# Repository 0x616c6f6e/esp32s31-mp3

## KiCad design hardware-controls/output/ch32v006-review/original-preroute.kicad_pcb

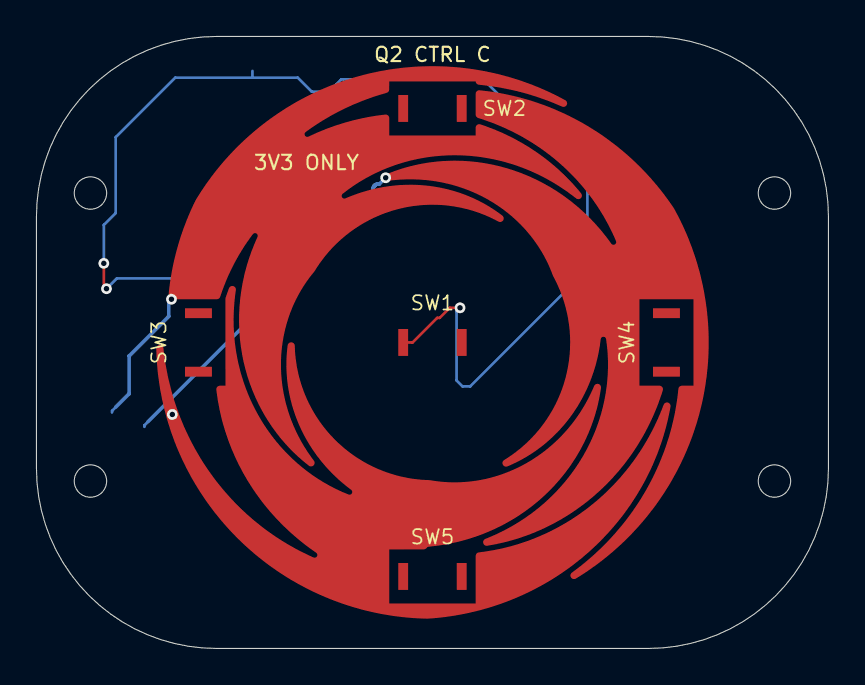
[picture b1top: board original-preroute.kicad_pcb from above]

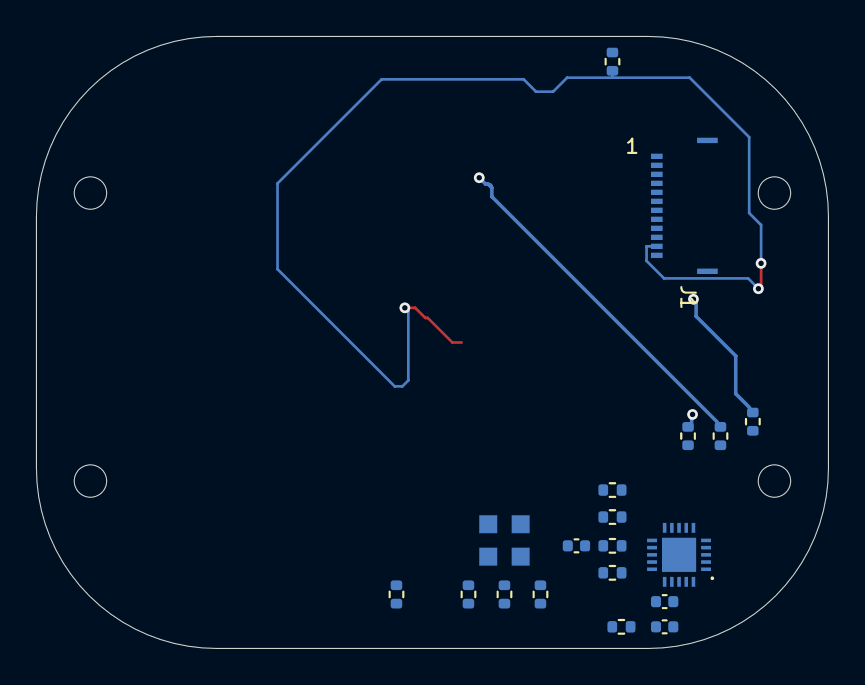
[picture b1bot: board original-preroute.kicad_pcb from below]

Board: 2 copper layers, 44.0 x 34.0 mm, 29 parts (19 on the bottom side), 19 nets.

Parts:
C1, C3: 100nF; C0402
C2: 1uF; C0402
E1: 31mm INTERPOLATED WHEEL; Wheel_D31
H1, H2, H3, H4: M1.6 / NPTH 1.8; Mount_1.8
J1: HC-FPC-05-10-12RLTAG; HCTL_FPC12
J2: WCH_SDI_PADS; SDI_4_Pads
R1, R2, R3: 1k; R0402
R4, R5: 4.7k; R0402
R6, R7, R14: 10k; R0402
R8: 0R; R0402
R9, R10, R11, R12: 47k; R0402
SW1, SW2, SW3, SW4, SW5: SKSWCEE010; SKSW_3x2
U1: CH32V006F8U6; CH32V006_QFN20

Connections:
/+3V3: J1.2, R4.1, R5.1, R6.1, R7.1, R8.1, R9.1, R10.1, R11.1, R12.1, R14.1
/GND: C1.2, C2.2, C3.2, J1.1, J1.12, J1.13 (SHIELD), J1.14 (SHIELD), J2.3 (GND), SW1.2, SW2.2, SW3.2, SW4.2, SW5.2, U1.0 (VSS_EP), U1.4 (VSS)
/INT_N: J1.5, R6.2, U1.7 (PC0/INT)
/KEY_BACK: R9.2, SW2.1, U1.10 (PC3)
/KEY_NEXT: R11.2, SW4.1, U1.13 (PC6)
/KEY_PLAY: R12.2, SW5.1, U1.14 (PC7)
/KEY_POWER: J1.11, R14.2, SW1.1
/KEY_PREV: R10.2, SW3.1, U1.12 (PC5)
/RESET_N: C3.1, J1.6, J2.4 (RESET_N), R7.2, U1.1 (PD7/~RST)
/SCL: J1.4, R5.2, U1.9 (PC2/SCL)
/SDA: J1.3, R4.2, U1.8 (PC1/SDA)
/SENSE0: R1.2, U1.16 (PD2/TKEY3)
/SENSE1: R2.2, U1.17 (PD3/TKEY4)
/SENSE2: R3.2, U1.18 (PD4/TKEY7)
/SWIO: J2.2 (SWIO), U1.15 (PD1/SWIO)
/VDD_MCU: C1.1, C2.1, J2.1 (VREF_3V3), R8.2, U1.6 (VDD)
/WHEEL0: E1.1 (CH0), R1.1
/WHEEL1: E1.2 (CH1), R2.1
/WHEEL2: E1.3 (CH2), R3.1

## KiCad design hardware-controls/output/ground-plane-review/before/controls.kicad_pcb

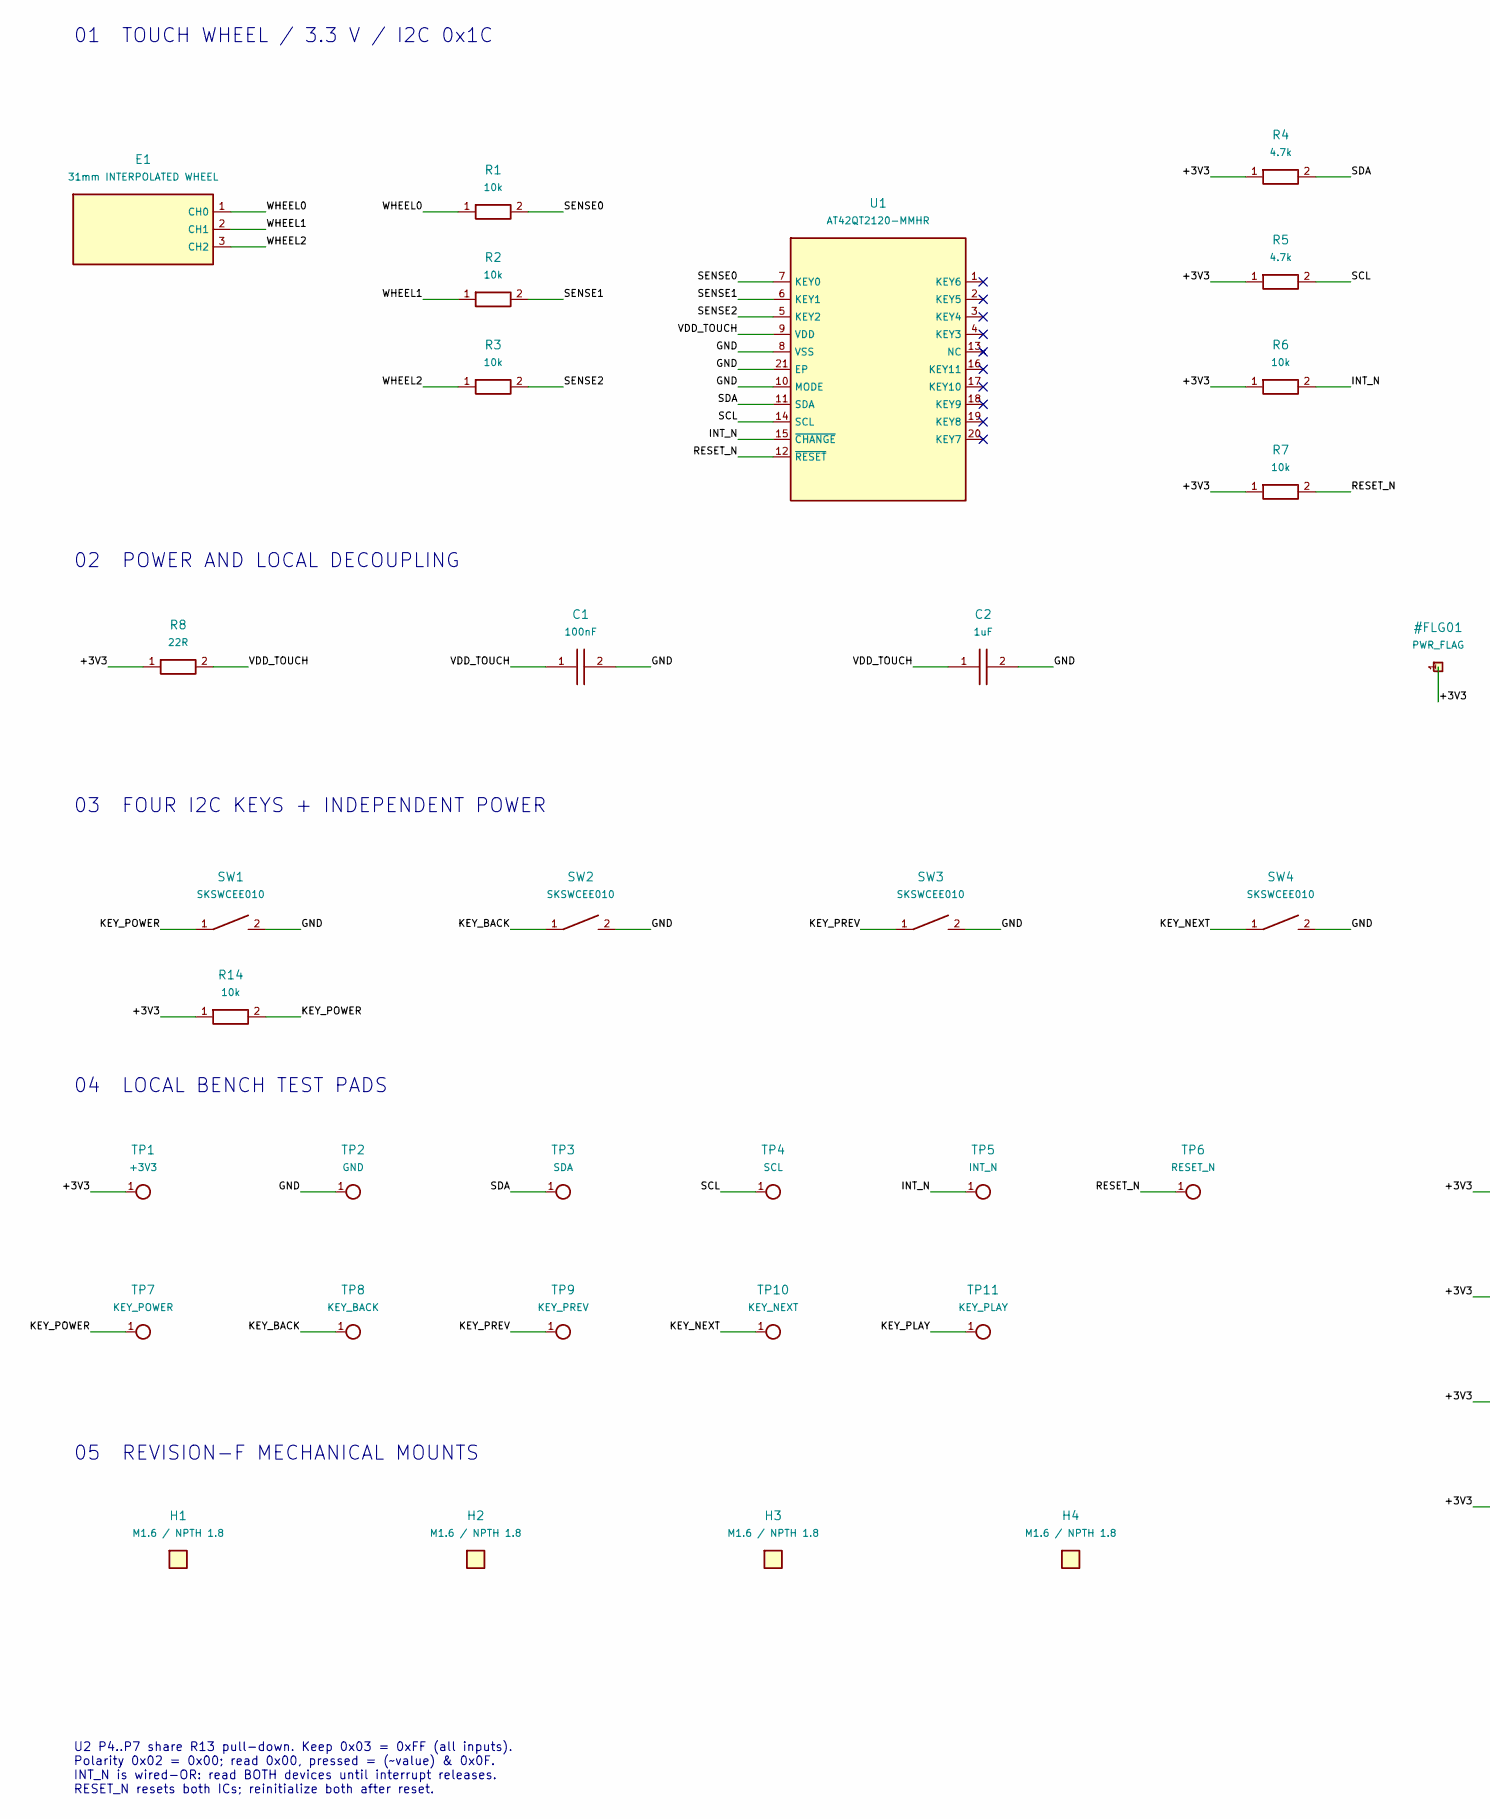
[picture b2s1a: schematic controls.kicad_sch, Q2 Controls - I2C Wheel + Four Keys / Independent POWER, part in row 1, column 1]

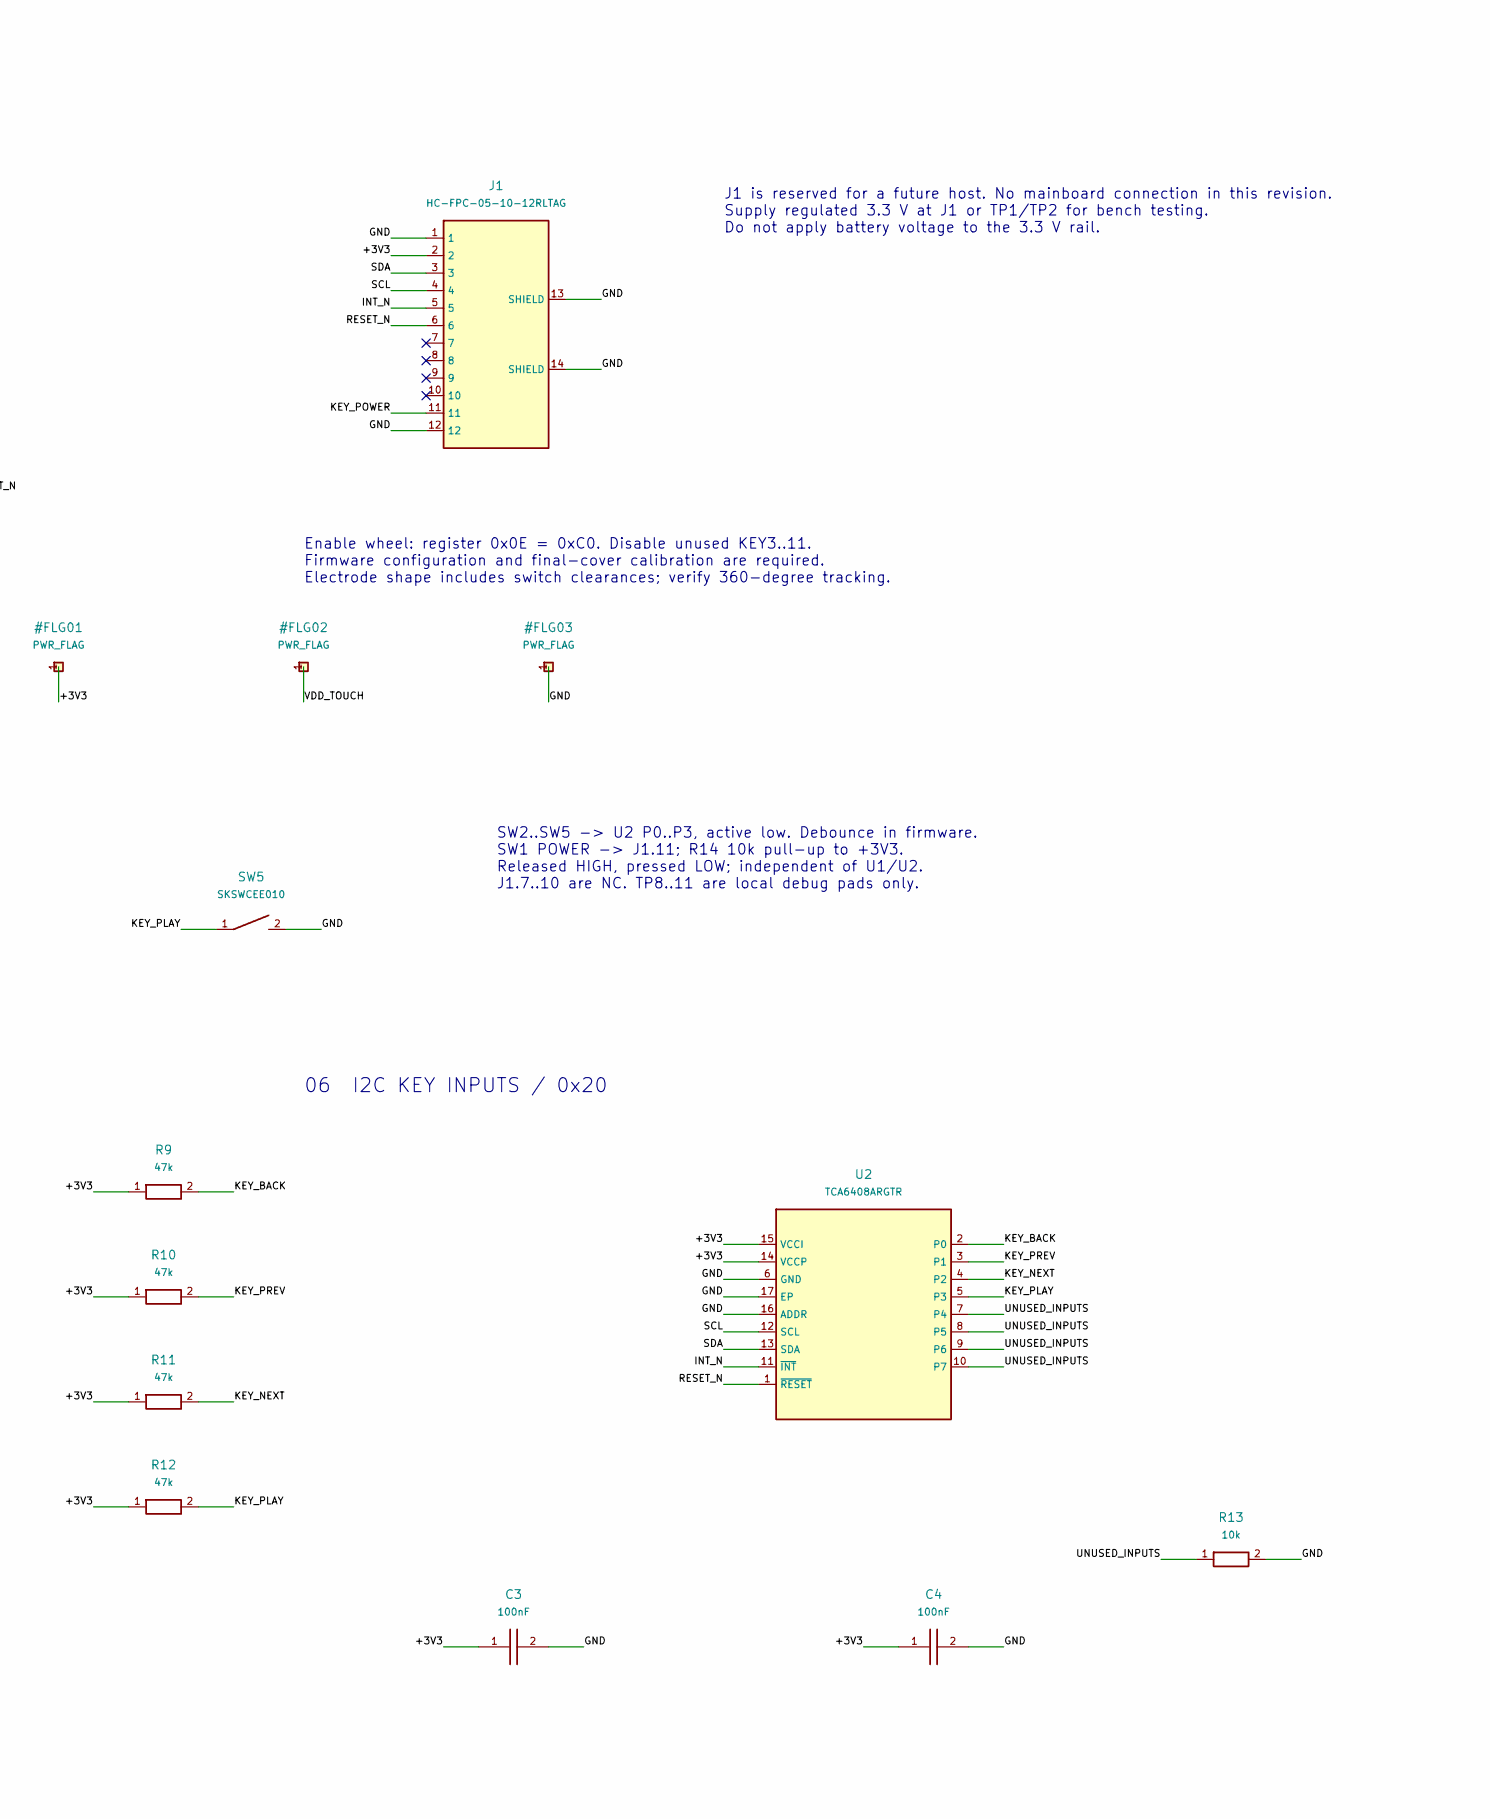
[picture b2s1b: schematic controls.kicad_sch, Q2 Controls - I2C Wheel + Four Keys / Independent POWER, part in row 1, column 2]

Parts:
C1, C3, C4: 100nF; C0402
C2: 1uF; C0402
E1: 31mm INTERPOLATED WHEEL; Wheel_D31
H1, H2, H3, H4: M1.6 / NPTH 1.8; Mount_1.8
J1: HC-FPC-05-10-12RLTAG; HCTL_FPC12
R1, R2, R3, R6, R7, R13, R14: 10k; R0402
R4, R5: 4.7k; R0402
R8: 22R; R0402
R9, R10, R11, R12: 47k; R0402
SW1, SW2, SW3, SW4, SW5: SKSWCEE010; SKSW_3x2
TP1: +3V3; TestPad
TP2: GND; TestPad
TP3: SDA; TestPad
TP4: SCL; TestPad
TP5: INT_N; TestPad
TP6: RESET_N; TestPad
TP7: KEY_POWER; TestPad
TP8: KEY_BACK; TestPad
TP9: KEY_PREV; TestPad
TP10: KEY_NEXT; TestPad
TP11: KEY_PLAY; TestPad
U1: AT42QT2120-MMHR; QT2120_VQFN20
U2: TCA6408ARGTR; TCA6408A_VQFN16

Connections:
/+3V3: C3.1, C4.1, J1.2, R4.1, R5.1, R6.1, R7.1, R8.1, R9.1, R10.1, R11.1, R12.1, R14.1, TP1.1, U2.14 (VCCP), U2.15 (VCCI)
/GND: C1.2, C2.2, C3.2, C4.2, J1.1, J1.12, J1.13 (SHIELD), J1.14 (SHIELD), R13.2, SW1.2, SW2.2, SW3.2, SW4.2, SW5.2, TP2.1, U1.8 (VSS), U1.10 (MODE), U1.21 (EP), U2.6 (GND), U2.16 (ADDR), U2.17 (EP)
/INT_N: J1.5, R6.2, TP5.1, U1.15 (~CHANGE), U2.11 (~INT)
/KEY_BACK: R9.2, SW2.1, TP8.1, U2.2 (P0)
/KEY_NEXT: R11.2, SW4.1, TP10.1, U2.4 (P2)
/KEY_PLAY: R12.2, SW5.1, TP11.1, U2.5 (P3)
/KEY_POWER: J1.11, R14.2, SW1.1, TP7.1
/KEY_PREV: R10.2, SW3.1, TP9.1, U2.3 (P1)
/RESET_N: J1.6, R7.2, TP6.1, U1.12 (~RESET), U2.1 (~RESET)
/SCL: J1.4, R5.2, TP4.1, U1.14 (SCL), U2.12 (SCL)
/SDA: J1.3, R4.2, TP3.1, U1.11 (SDA), U2.13 (SDA)
/SENSE0: R1.2, U1.7 (KEY0)
/SENSE1: R2.2, U1.6 (KEY1)
/SENSE2: R3.2, U1.5 (KEY2)
/UNUSED_INPUTS: R13.1, U2.7 (P4), U2.8 (P5), U2.9 (P6), U2.10 (P7)
/VDD_TOUCH: C1.1, C2.1, R8.2, U1.9 (VDD)
/WHEEL0: E1.1 (CH0), R1.1
/WHEEL1: E1.2 (CH1), R2.1
/WHEEL2: E1.3 (CH2), R3.1

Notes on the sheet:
01 TOUCH WHEEL / 3.3 V / I2C 0x1C
02 POWER AND LOCAL DECOUPLING
03 FOUR I2C KEYS + INDEPENDENT POWER
04 LOCAL BENCH TEST PADS
05 REVISION-F MECHANICAL MOUNTS
06 I2C KEY INPUTS / 0x20
J1 is reserved for a future host. No mainboard connection in this revision. Supply regulated 3.3 V at J1 or TP1/TP2 for bench testing. Do not apply battery voltage to the 3.3 V rail.
SW2..SW5 -> U2 P0..P3, active low. Debounce in firmware. SW1 POWER -> J1.11; R14 10k pull-up to +3V3. Released HIGH, pressed LOW; independent of U1/U2. J1.7..10 are NC. TP8..11 are local debug pads only.
Enable wheel: register 0x0E = 0xC0. Disable unused KEY3..11. Firmware configuration and final-cover calibration are required. Electrode shape includes switch clearances; verify 360-degree tracking.
U2 P4..P7 share R13 pull-down. Keep 0x03 = 0xFF (all inputs). Polarity 0x02 = 0x00; read 0x00, pressed = (~value) & 0x0F. INT_N is wired-OR: read BOTH devices until interrupt releases. RESET_N resets both ICs; reinitialize both after reset.

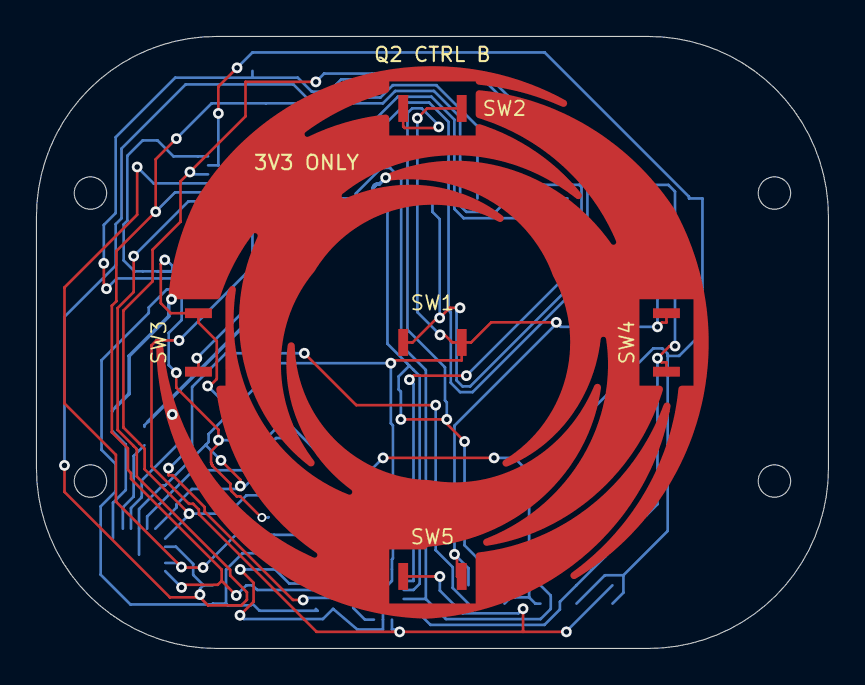
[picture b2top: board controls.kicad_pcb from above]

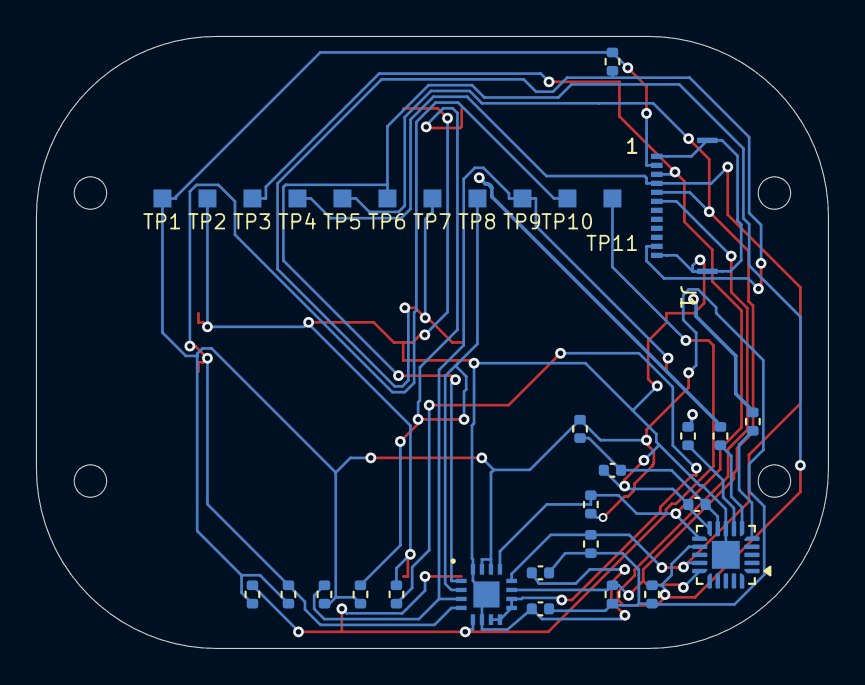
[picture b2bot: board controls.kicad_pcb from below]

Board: 2 copper layers, 44.0 x 34.0 mm, 42 parts (32 on the bottom side), 19 nets.
